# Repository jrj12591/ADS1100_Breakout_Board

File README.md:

# ADS1100_Breakout_Board
ADS1100 Breakout Board

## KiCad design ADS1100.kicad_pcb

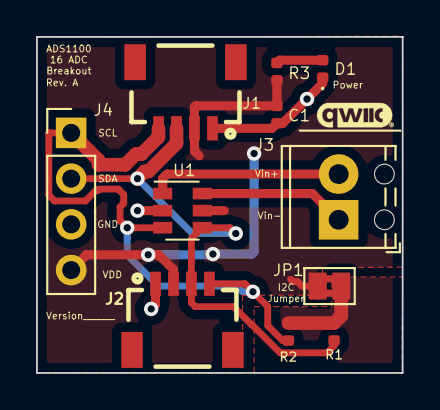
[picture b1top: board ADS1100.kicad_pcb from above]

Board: 2 copper layers, 20.3 x 18.7 mm, 11 parts (0 on the bottom side), 8 nets.

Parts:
C1: C; C_0402_1005Metric
D1: LED; LED_0402_1005Metric
J1, J2: I2C_STANDARDQWIIC; 1X04_1MM_RA
J3: Conn_01x02; TerminalBlock_Phoenix_MPT-0,5-2-2.54_1x02_P2.54mm_Horizontal
J4: Conn_01x04; PinHeader_1x04_P2.54mm_Vertical
JP1: Jumper_2_Bridged; SolderJumper-2_P1.3mm_Bridged2Bar_Pad1.0x1.5mm
R1, R2, R3: R; R_0402_1005Metric
U1: ADS1100A0; SOT-23-6

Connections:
+3V3: C1.1, J1.2, J2.2, J4.4, JP1.1, R3.1, U1.5
GND: C1.2, D1.1, J1.1, J2.1, J4.3, U1.2
unnamed: D1.2, R3.2
unnamed: J3.1, U1.6
unnamed: J3.2, U1.1
unnamed: JP1.2, R1.1, R2.1
SCL: J1.4, J2.4, J4.1, R2.2, U1.3
SDA: J1.3, J2.3, J4.2, R1.2, U1.4

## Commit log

2020-03-25 inital upload
